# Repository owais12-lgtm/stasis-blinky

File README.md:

# about
This is a keychain with a buncha leds in the shape of the stasis logo! 

# Images

# BOM
| Name                | Purpose                  | Quantity | Total Cost (USD) |
|---------------------|--------------------------|----------|------------------|
| NE555P              | Timer IC                 | 1        | $0.50            |
| CD4017BE            | Decade Counter IC        | 1        | $1.00            |
| Conn_01x02_Socket   | Power Header             | 2        | $0.80            |
| Conn_01x01_Socket   | Debug Header             | 1        | $0.20            | 
| C_Polarized         | Electrolytic Capacitor   | 1        | $0.30            | 
| C                   | Ceramic Capacitor        | 1        | $0.20            | 
| R 1kΩ               | Resistor                 | 1        | $0.10            | 
| R 470Ω              | Resistor                 | 1        | $0.10            |
| RV (Potentiometer)  | Variable Resistor        | 1        | $0.80            | 
| LED (x10 Red)       | LED                      | 10       | $10.00           | 
| LED (x10 Orange)    | LED                      | 10       | $10.00           | 
| LED (x10 Yellow)    | LED                      | 10       | $10.00           | 
| LED (x10 Emerald)   | LED                      | 10       | $10.00           | 
| LED (x10 Blue)      | LED                      | 10       | $10.00           | 
| **TOTAL**           |                          |          | **$54.00**       |   

note: this does not require firmware or a case.

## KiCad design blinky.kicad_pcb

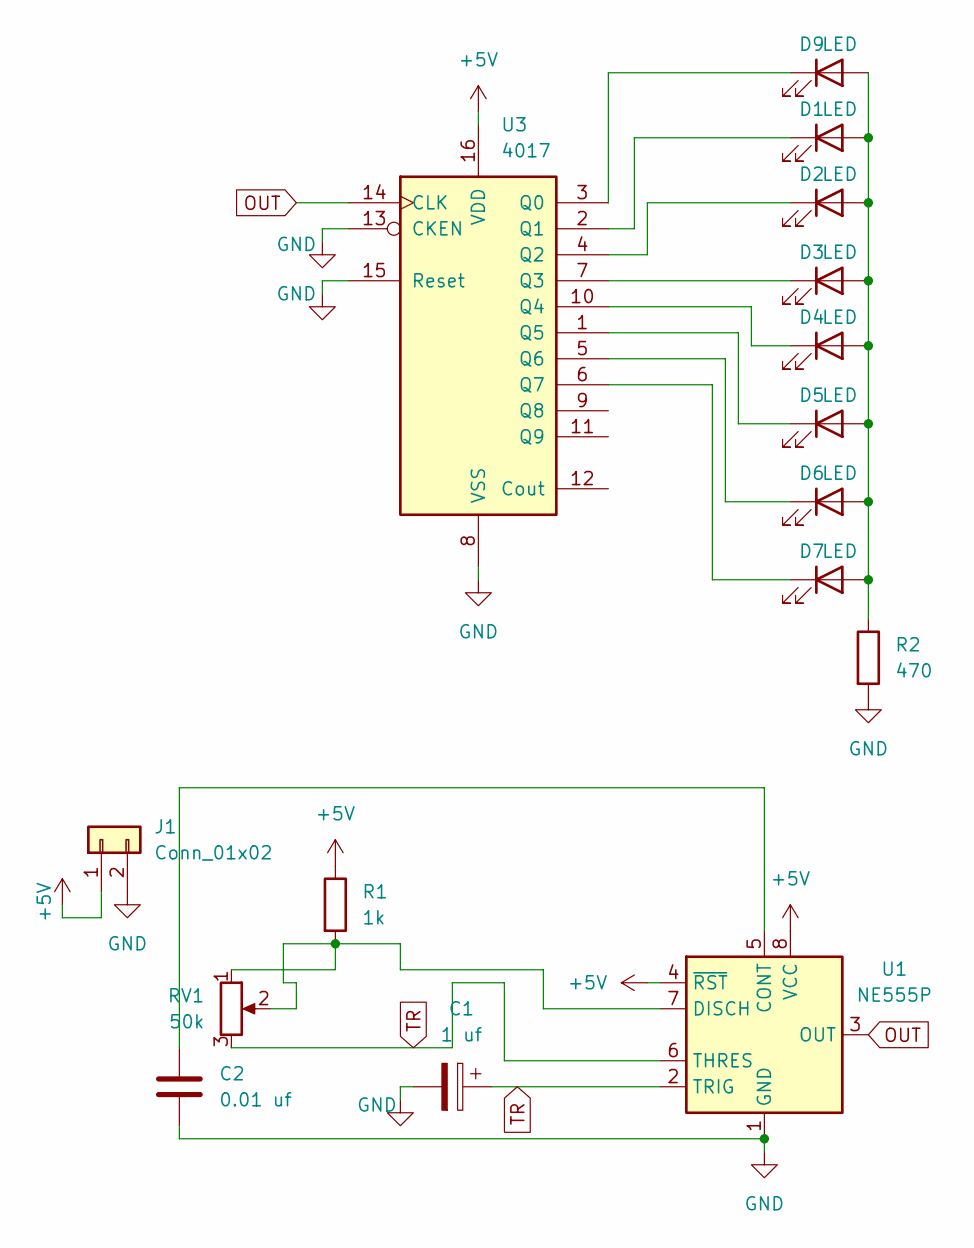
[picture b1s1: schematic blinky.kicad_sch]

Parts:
C1: 1 uf; CP_Radial_D5.0mm_P2.00mm
C2: 0.01 uf; C_Disc_D7.5mm_W2.5mm_P5.00mm
D1, D2, D3, D4, D5, D6, D7, D9: LED; LED_D3.0mm
J1: Conn_01x02; PinHeader_1x02_P2.54mm_Vertical
R1: 1k; R_Axial_DIN0207_L6.3mm_D2.5mm_P7.62mm_Horizontal
R2: 470; R_Axial_DIN0207_L6.3mm_D2.5mm_P7.62mm_Horizontal
RV1: 50k; Potentiometer_ACP_CA6-VSMD_Vertical
U1: NE555P; DIP-8_W7.62mm
U3: 4017; N16

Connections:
+5V: J1.1, R1.1, U1.4 (~RST), U1.8 (VCC), U3.16 (VDD)
GND: C1.2, C2.2, J1.2, R2.2, U1.1 (GND), U3.8 (VSS), U3.13 (CKEN), U3.15 (Reset)
unnamed: D1.2 (A), D2.2 (A), D3.2 (A), D4.2 (A), D5.2 (A), D6.2 (A), D7.2 (A), D9.2 (A), R2.1
unnamed: D1.1 (K), U3.2 (Q1)
unnamed: D2.1 (K), U3.4 (Q2)
unnamed: D3.1 (K), U3.7 (Q3)
unnamed: D4.1 (K), U3.10 (Q4)
unnamed: D5.1 (K), U3.1 (Q5)
unnamed: D6.1 (K), U3.5 (Q6)
unnamed: D7.1 (K), U3.6 (Q7)
unnamed: D9.1 (K), U3.3 (Q0)
unnamed: C2.1, U1.5 (CONT)
unnamed: R1.2, RV1.1, RV1.2, U1.7 (DISCH)
OUT: U1.3 (OUT), U3.14 (CLK)
TR: C1.1, RV1.3, U1.2 (TRIG), U1.6 (THRES)

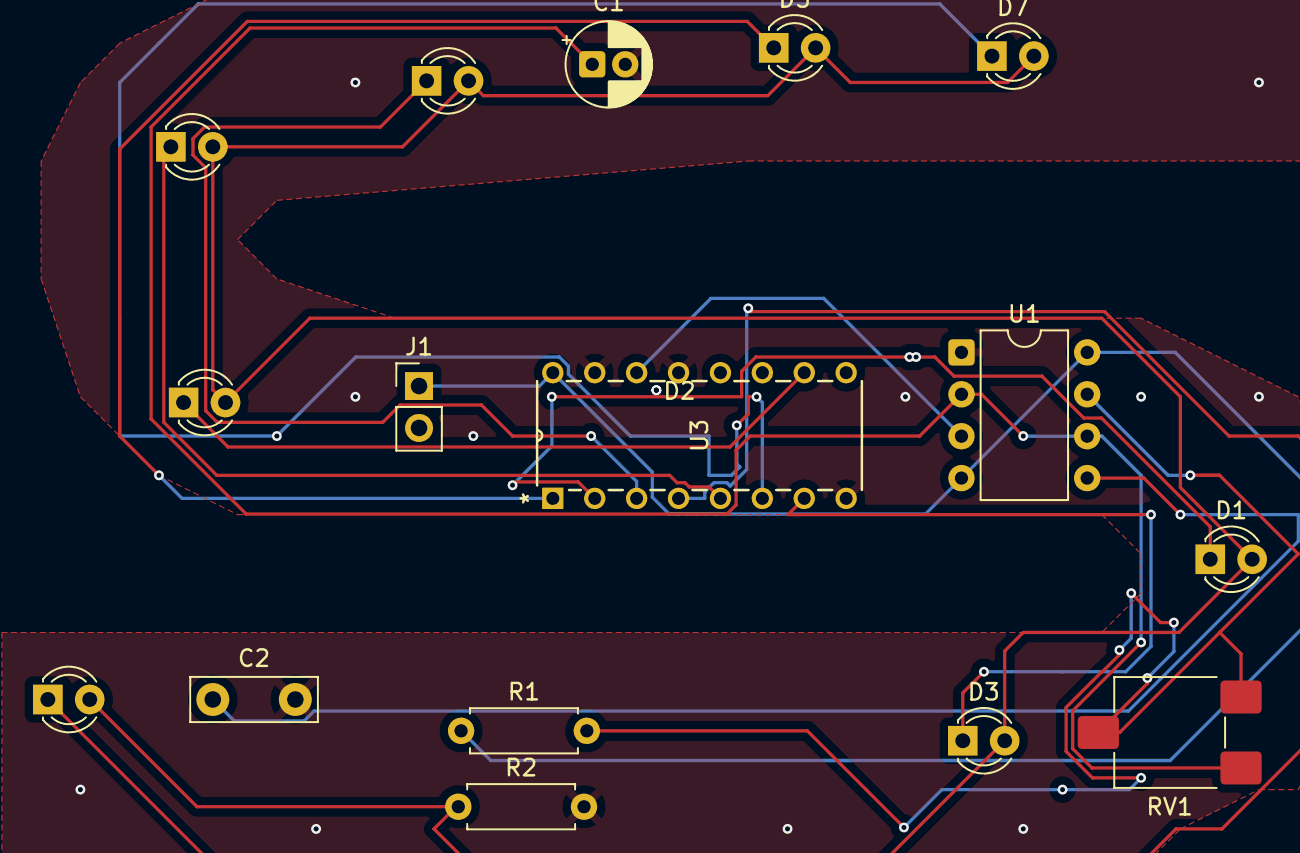
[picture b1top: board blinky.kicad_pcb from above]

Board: 2 copper layers, 16 parts (0 on the bottom side), 15 nets.
